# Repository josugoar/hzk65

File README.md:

# hzk65

<h1></h1>

> Modular assembly 65% keyboard

HizKey65 ([/is̻ki/](https://hiztegiak.elhuyar.eus/eu/hizki)) is a modular assembly 65% keyboard with a socketed controller, hot-swap switch sockets, sandwich-mounted case and ANSI layout.

Built with [KiCad](https://www.kicad.org/) and [FreeCAD](https://www.freecad.org/) and manufactured by [JLC Digital Manufacturing](https://jlcpcb.com/).

> [!NOTE]
> Enclose the controller in an acrylic housing or use conformal coating for enhanced protection

## Latest revisions

- hzk65: for Cherry MX compatible switches

  - Rev. A (Hotswappable)

## Layout

*[KLE layout](https://www.keyboard-layout-editor.com/##@@_c=%23777777%3B&=0,0&_c=%23cccccc%3B&=0,1&=0,2&=0,3&=0,4&=0,5&=0,6&=0,7&=0,8&=0,9&=0,10&=0,11&=0,12&_c=%23aaaaaa&w:2%3B&=0,13%3B&@_w:1.5%3B&=1,0&_c=%23cccccc%3B&=1,1&=1,2&=1,3&=1,4&=1,5&=1,6&=1,7&=1,8&=1,9&=1,10&=1,11&=1,12&_w:1.5%3B&=1,13%3B&@_c=%23aaaaaa&w:1.75%3B&=2,0&_c=%23cccccc%3B&=2,1&=2,2&=2,3&=2,4&=2,5&=2,6&=2,7&=2,8&=2,9&=2,10&=2,11&_c=%23777777&w:2.25%3B&=2,13%3B&@_c=%23aaaaaa&w:2.25%3B&=3,0&_c=%23cccccc%3B&=3,2&=3,3&=3,4&=3,5&=3,6&=3,7&=3,8&=3,9&=3,10&=3,11&_c=%23aaaaaa&w:1.75%3B&=3,12&_x:1.5&c=%23777777%3B&=3,14%3B&@_y:-0.75&x:14.25%3B&=3,13%3B&@_y:-0.25&c=%23aaaaaa&w:1.25%3B&=4,0&_w:1.25%3B&=4,1&_w:1.25%3B&=4,2&_c=%23cccccc&w:6.25&%2F_rs:180%3B&=4,6&_c=%23aaaaaa%3B&=4,9&=4,10&=4,11%3B&@_y:-0.75&x:13.25&c=%23777777%3B&=4,12&=4,13&=4,14)*

## PCB

*Top view*

*Bottom view*

## Assembly

*Top view*

*Bottom view*

*Side view*

## Credits

- [CherryMx](https://github.com/hineybush/CherryMX): MX profile keycap 3D models

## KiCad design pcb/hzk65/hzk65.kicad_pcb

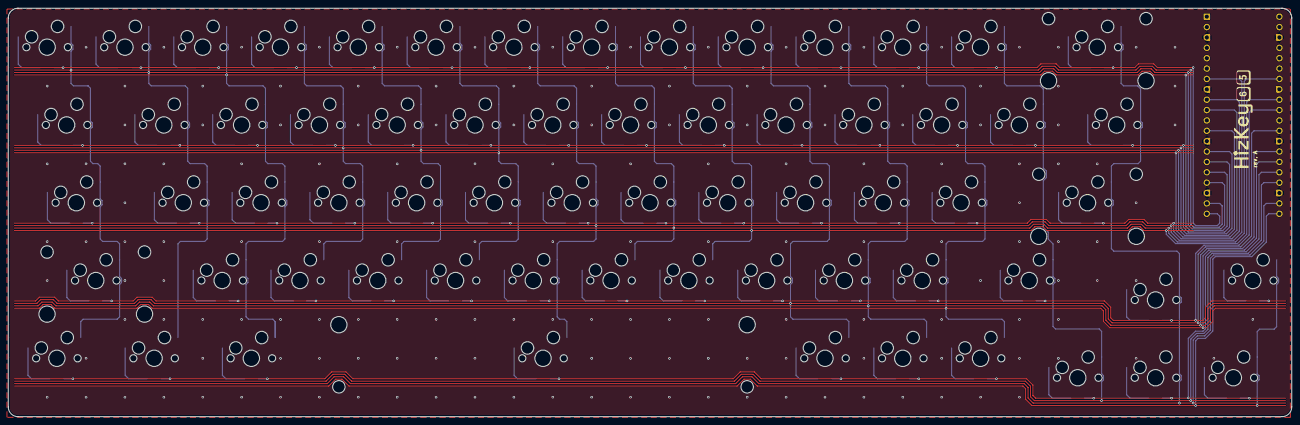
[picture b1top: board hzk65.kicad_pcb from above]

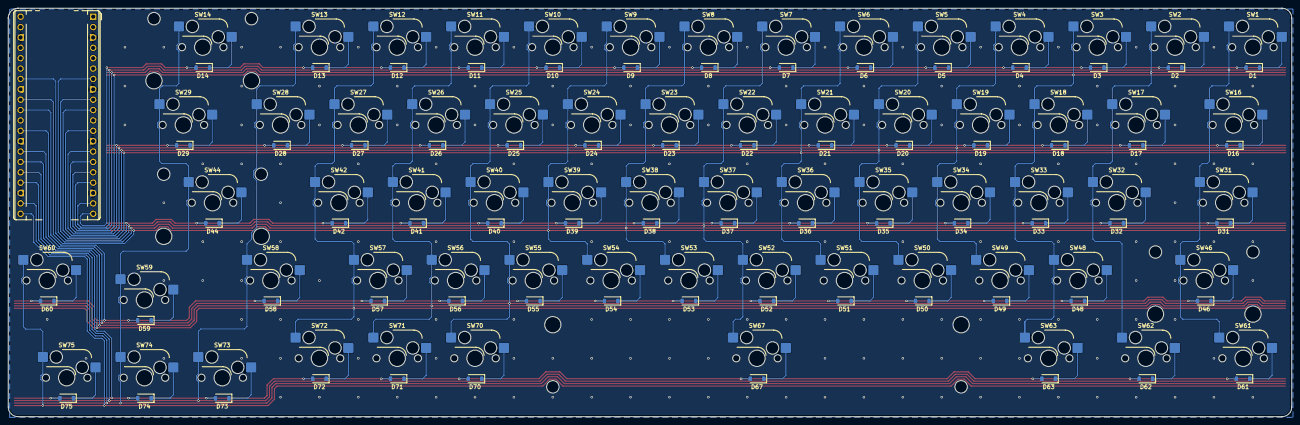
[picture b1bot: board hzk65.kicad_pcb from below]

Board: 2 copper layers, 314.3 x 100.0 mm, 135 parts (65 on the bottom side), 86 nets.

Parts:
A1: RaspberryPi_Pico; RaspberryPi_Pico_Common_THT
D1, D2, D3, D4, D5, D6, D7, D8, D9, D10, D11, D12, D13, D14, D16, D17, D18, D19, D20, D21, D22, D23, D24, D25, D26, D27, D28, D29, D31, D32, D33, D34, D35, D36, D37, D38, D39, D40, D41, D42, D44, D46, D48, D49, D50, D51, D52, D53, D54, D55, D56, D57, D58, D59, D60, D61, D62, D63, D67, D70, D71, D72, D73, D74, D75: 1N4148; D_SOD-123
H14, H46: Stabilizer_Cherry_MX_2.00u
H44: m; Stabilizer_Cherry_MX_2.00u
H67: Stabilizer_Cherry_MX_6.25u
SW1, SW2, SW3, SW4, SW5, SW6, SW7, SW8, SW9, SW10, SW11, SW12, SW13, SW17, SW18, SW19, SW20, SW21, SW22, SW23, SW24, SW25, SW26, SW27, SW28, SW32, SW33, SW34, SW35, SW36, SW37, SW38, SW39, SW40, SW41, SW42, SW48, SW49, SW50, SW51, SW52, SW53, SW54, SW55, SW56, SW57, SW59, SW60, SW70, SW71, SW72, SW73, SW74, SW75: SW_Push; SW_Hotswap_Kailh_MX_1.00u
SW14: SW_Push; SW_Hotswap_Kailh_MX_2.00u
SW16, SW29: SW_Push; SW_Hotswap_Kailh_MX_1.50u
SW31, SW58: SW_Push; SW_Hotswap_Kailh_MX_1.75u
SW44, SW46: SW_Push; SW_Hotswap_Kailh_MX_2.25u
SW61, SW62, SW63: SW_Push; SW_Hotswap_Kailh_MX_1.25u
SW67: SW_Push; SW_Hotswap_Kailh_MX_6.25u

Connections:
/COL0: A1.19 (GPIO14), SW1.2, SW16.2, SW31.2, SW46.2, SW61.2
/COL1: A1.17 (GPIO13), SW2.2, SW17.2, SW32.2, SW62.2
/COL2: A1.16 (GPIO12), SW3.2, SW18.2, SW33.2, SW48.2, SW63.2
/COL3: A1.14 (GPIO10), SW4.2, SW19.2, SW34.2, SW49.2
/COL4: A1.12 (GPIO9), SW5.2, SW20.2, SW35.2, SW50.2
/COL5: A1.10 (GPIO7), SW6.2, SW21.2, SW36.2, SW51.2
/COL6: A1.7 (GPIO5), SW7.2, SW22.2, SW37.2, SW52.2, SW67.2
/COL7: A1.34 (GPIO28_ADC2), SW8.2, SW23.2, SW38.2, SW53.2
/COL8: A1.32 (GPIO27_ADC1), SW9.2, SW24.2, SW39.2, SW54.2
/COL9: A1.29 (GPIO22), SW10.2, SW25.2, SW40.2, SW55.2, SW70.2
/COL10: A1.27 (GPIO21), SW11.2, SW26.2, SW41.2, SW56.2, SW71.2
/COL11: A1.26 (GPIO20), SW12.2, SW27.2, SW42.2, SW57.2, SW72.2
/COL12: A1.24 (GPIO18), SW13.2, SW28.2, SW58.2, SW73.2
/COL13: A1.22 (GPIO17), SW14.2, SW29.2, SW44.2, SW59.2, SW74.2
/COL14: A1.21 (GPIO16), SW60.2, SW75.2
/ROW0: A1.20 (GPIO15), D1.2 (A), D2.2 (A), D3.2 (A), D4.2 (A), D5.2 (A), D6.2 (A), D7.2 (A), D8.2 (A), D9.2 (A), D10.2 (A), D11.2 (A), D12.2 (A), D13.2 (A), D14.2 (A)
/ROW1: A1.15 (GPIO11), D16.2 (A), D17.2 (A), D18.2 (A), D19.2 (A), D20.2 (A), D21.2 (A), D22.2 (A), D23.2 (A), D24.2 (A), D25.2 (A), D26.2 (A), D27.2 (A), D28.2 (A), D29.2 (A)
/ROW2: A1.9 (GPIO6), D31.2 (A), D32.2 (A), D33.2 (A), D34.2 (A), D35.2 (A), D36.2 (A), D37.2 (A), D38.2 (A), D39.2 (A), D40.2 (A), D41.2 (A), D42.2 (A), D44.2 (A)
/ROW3: A1.31 (GPIO26_ADC0), D46.2 (A), D48.2 (A), D49.2 (A), D50.2 (A), D51.2 (A), D52.2 (A), D53.2 (A), D54.2 (A), D55.2 (A), D56.2 (A), D57.2 (A), D58.2 (A), D59.2 (A), D60.2 (A)
/ROW4: A1.25 (GPIO19), D61.2 (A), D62.2 (A), D63.2 (A), D67.2 (A), D70.2 (A), D71.2 (A), D72.2 (A), D73.2 (A), D74.2 (A), D75.2 (A)
GND: A1.3 (GND), A1.8 (GND), A1.13 (GND), A1.18 (GND), A1.23 (GND), A1.28 (GND), A1.38 (GND)
unnamed: D1.1 (K), SW1.1
unnamed: D2.1 (K), SW2.1
unnamed: D3.1 (K), SW3.1
unnamed: D4.1 (K), SW4.1
unnamed: D5.1 (K), SW5.1
unnamed: D6.1 (K), SW6.1
unnamed: D7.1 (K), SW7.1
unnamed: D8.1 (K), SW8.1
unnamed: D9.1 (K), SW9.1
unnamed: D10.1 (K), SW10.1
unnamed: D11.1 (K), SW11.1
unnamed: D12.1 (K), SW12.1
unnamed: D13.1 (K), SW13.1
unnamed: D14.1 (K), SW14.1
unnamed: D16.1 (K), SW16.1
unnamed: D17.1 (K), SW17.1
unnamed: D18.1 (K), SW18.1
unnamed: D19.1 (K), SW19.1
unnamed: D20.1 (K), SW20.1
unnamed: D21.1 (K), SW21.1
unnamed: D22.1 (K), SW22.1
unnamed: D23.1 (K), SW23.1
unnamed: D24.1 (K), SW24.1
unnamed: D25.1 (K), SW25.1
unnamed: D26.1 (K), SW26.1
unnamed: D27.1 (K), SW27.1
unnamed: D28.1 (K), SW28.1
unnamed: D29.1 (K), SW29.1
unnamed: D31.1 (K), SW31.1
unnamed: D32.1 (K), SW32.1
unnamed: D33.1 (K), SW33.1
unnamed: D34.1 (K), SW34.1
unnamed: D35.1 (K), SW35.1
unnamed: D36.1 (K), SW36.1
unnamed: D37.1 (K), SW37.1
unnamed: D38.1 (K), SW38.1
unnamed: D39.1 (K), SW39.1
unnamed: D40.1 (K), SW40.1
unnamed: D41.1 (K), SW41.1
unnamed: D42.1 (K), SW42.1
unnamed: D44.1 (K), SW44.1
unnamed: D46.1 (K), SW46.1
unnamed: D48.1 (K), SW48.1
unnamed: D49.1 (K), SW49.1
unnamed: D50.1 (K), SW50.1
unnamed: D51.1 (K), SW51.1
unnamed: D52.1 (K), SW52.1
unnamed: D53.1 (K), SW53.1
unnamed: D54.1 (K), SW54.1
unnamed: D55.1 (K), SW55.1
unnamed: D56.1 (K), SW56.1
unnamed: D57.1 (K), SW57.1
unnamed: D58.1 (K), SW58.1
unnamed: D59.1 (K), SW59.1
unnamed: D60.1 (K), SW60.1
unnamed: D61.1 (K), SW61.1
unnamed: D62.1 (K), SW62.1
unnamed: D63.1 (K), SW63.1
unnamed: D67.1 (K), SW67.1
unnamed: D70.1 (K), SW70.1
unnamed: D71.1 (K), SW71.1
unnamed: D72.1 (K), SW72.1
unnamed: D73.1 (K), SW73.1
unnamed: D74.1 (K), SW74.1
unnamed: D75.1 (K), SW75.1

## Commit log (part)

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2026-06-20 Add keyboard layout editor raw data
2026-06-20 Use original formatting
2026-06-21 Add ansi layout
2026-06-21 Add iso layout
2026-06-21 Add multi-layout
2026-06-21 Use json extension
2026-06-21 Add kicad schematic
2026-06-21 Rename sheets
2026-06-21 Update matrix positions
2026-06-23 Rename gr65_ansi.json to gr65.json
2026-06-28 Add mcu decal
2026-06-28 Rotate spacebar
2026-06-28 Add bom
